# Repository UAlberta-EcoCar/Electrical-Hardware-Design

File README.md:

View this project on [CADLAB.io](https://cadlab.io/project/29517). 

# Electrical-Design-Hardware

**Do not merge branches to main yet, this may be done in the future**

Contains the hardware design for the upcoming prototype vehicle.  Each Branch in this repo has its own board design and schematic files for each car.  Add the entire repo to a filepath ia GitHub Desktop by adding the link into the "Current Repository" panel or with the following via a console:

```
cd Documents\GitHub                                                            #Change your directory where desired
git clone https://github.com/UAlberta-EcoCar/Electrical-Hardware-Design        #Clone the repo
cd Documents\GitHub\Electrical-Hardware-Design                                 #Change your directory into the repo
git branch -r                                                                  #Displays all remote branches, choose the branch you're looking for 
git checkout Relay-Board                                                       #branch that is desired (I used Relay-Board as an example).  
```
After making changes the remote branch can be updated with the following:
```
git add .                                                                      #Adds your modified files to the quene to be committed later
git commit -m "your-commit-message"                                            #Commits the files to a new revision of the branch with a log
git push                                                                       #Pushes the changes to the remote repo

#The following will pull the newest version of the remote repo:
git pull
```

If you want to see your local branches that you pulled or if you want to switch local branches do the following:

```
git branch                                                                     #Shows local branches (add -r for remote branches)
git switch <name-of-branch>                                                    #Switches branch

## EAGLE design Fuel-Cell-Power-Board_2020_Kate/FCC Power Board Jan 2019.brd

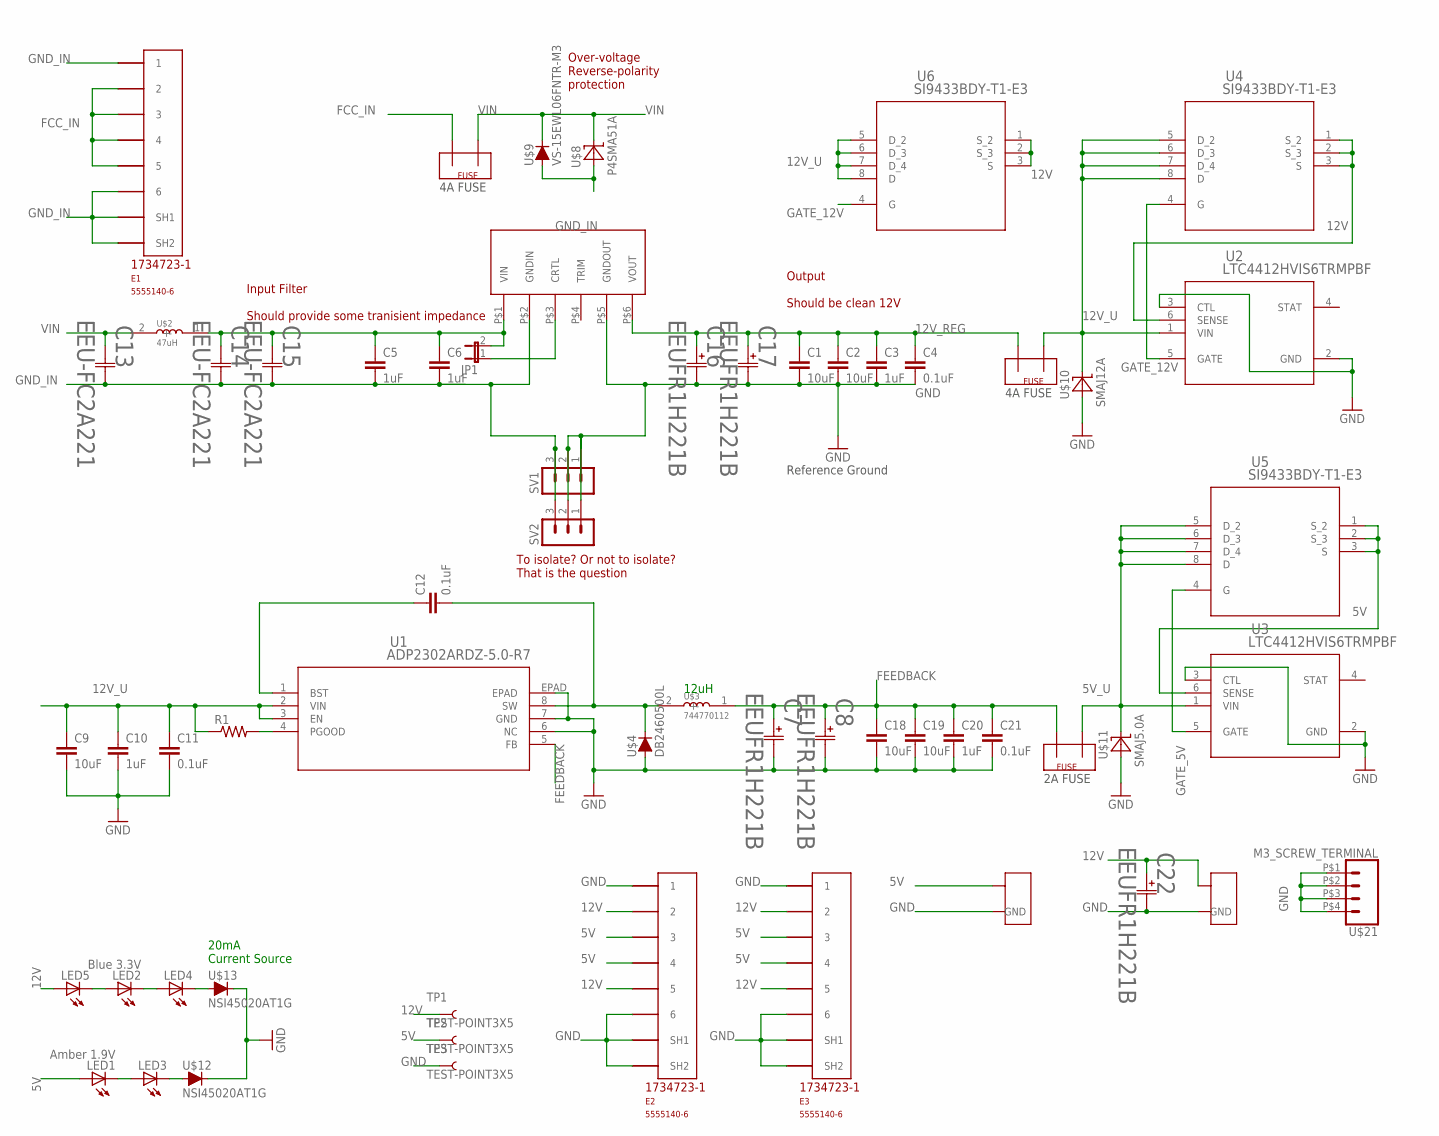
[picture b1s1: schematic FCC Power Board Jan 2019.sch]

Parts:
C1, C2, C9, C18, C19: 10uF; C1210
C3, C10, C20: 1uF; C0805
C4, C11, C12, C21: 0.1uF; C0603
C5, C6: 1uF; C1210
C7, C8, C16, C17, C22: EEUFR1H221B; CAP_PAN_10X16
C13, C14, C15: EEU-FC2A221; CAP_16_X_25
E1, E2, E3: 5555140-6; 1734723-1_RJ11
JP1: JP1E; JP1
LED1: Amber 1.9V; CHIPLED_0805
LED2: Blue 3.3V; CHIPLED_0805
LED3, LED4, LED5: LEDCHIPLED_0805; CHIPLED_0805
R1: R-US_R0603; R0603
SV1, SV2: MA03-1
TP1, TP2, TP3: TEST-POINT3X5; PAD.03X.05
U1: ADP2302ARDZ-5.0-R7; RD_8_1
U2, U3: LTC4412HVIS6TRMPBF; TSOT-23_S6
U4, U5, U6: SI9433BDY-T1-E3; SOIC-N-8_SI
U$1: RPA60-2412SFW_P; RPA60-2412SFW/P
U$2: 47uH; INDUCTOR_SMD_FOOTPRINT
U$3: 744770112; INDUCTOR_SMD_FOOTPRINT
U$4: DB2460500L; SOD123
U$5, U$6, U$7: SHELL2013_FUSEMINI-BLADE; SHELL2013_MINI-BLADE-FUSE
U$8: P4SMA51A; SMA-DO214AC
U$9: VS-15EWL06FNTR-M3; TO252
U$10: SMAJ12A; SMA-DO214AC
U$11: SMAJ5.0A; SMA-DO214AC
U$12, U$13: NSI45020AT1G; SOD123
U$18, U$20: 2X1-CONN; 2X1-MATE-N-LOCK
U$21: M3_SCREW_TERMINAL

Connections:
5V: E2.3, E2.4, E3.3, E3.4, LED1.A, TP2.P$1, U3.6 (SENSE), U5.1 (S_2), U5.2 (S_3), U5.3 (S), U$18.CIRCUIT1
5V_U: U3.1 (VIN), U5.5 (D_2), U5.6 (D_3), U5.7 (D_4), U5.8 (D), U$5.OUT, U$11.K (C)
12V: C22.1 (11), E2.2, E2.5, E3.2, E3.5, LED5.A, TP1.P$1, U2.6 (SENSE), U4.1 (S_2), U4.2 (S_3), U4.3 (S), U6.1 (S_2), U6.2 (S_3), U6.3 (S), U$20.CIRCUIT1
12V_REG: C1.1, C2.1, C3.1, C4.1, C16.1 (11), C17.1 (11), U$1.P$6 (VOUT), U$7.OUT
12V_U: C9.1, C10.1, C11.1, R1.1, U1.2 (VIN), U1.3 (EN), U2.1 (VIN), U4.5 (D_2), U4.6 (D_3), U4.7 (D_4), U4.8 (D), U6.5 (D_2), U6.6 (D_3), U6.7 (D_4), U6.8 (D), U$7.IN, U$10.K (C)
FCC_IN: E1.2, E1.3, E1.4, E1.5, U$6.OUT
FEEDBACK: C7.1 (11), C8.1 (11), C18.1, C19.1, C20.1, C21.1, U1.5 (FB), U$3.1 (+), U$5.IN
GATE_5V: U3.5 (GATE), U5.4 (G)
GATE_12V: U2.5 (GATE), U4.4 (G), U6.4 (G)
GND: C1.2, C2.2, C3.2, C4.2, C7.2 (22), C8.2 (22), C9.2, C10.2, C11.2, C16.2 (22), C17.2 (22), C18.2, C19.2, C20.2, C21.2, C22.2 (22), E2.1, E2.6, E2.SH1, E2.SH2, E3.1, E3.6, E3.SH1, E3.SH2, SV1.1, SV1.2, SV2.1, SV2.2, TP3.P$1, U1.6 (NC), U1.7 (GND), U1.EPAD, U2.2 (GND), U2.3 (CTL), U3.2 (GND), U3.3 (CTL), U$1.P$5 (GNDOUT), U$4.A, U$10.A, U$11.A, U$12.C, U$13.C, U$18.GND, U$20.GND, U$21.P$1 (1), U$21.P$2 (2), U$21.P$3 (3), U$21.P$4 (4)
GND_IN: C5.2, C6.2, C13.2 (22), C14.2 (22), C15.2 (22), E1.1, E1.6, E1.SH1, E1.SH2, SV1.3, SV2.3, U$1.P$2 (GNDIN), U$8.A, U$9.1 (A), U$9.2 (A)
unnamed: JP1.1, U$1.P$3 (CRTL)
unnamed: C12.1, U1.1 (BST)
unnamed: C12.2, U1.8 (SW), U$3.2 (-), U$4.C
unnamed: R1.2, U1.4 (PGOOD)
unnamed: LED1.C, LED3.A
unnamed: LED3.C, U$12.A
unnamed: LED4.C, U$13.A
unnamed: LED2.C, LED4.A
unnamed: LED2.A, LED5.C
unnamed: C5.1, C6.1, C14.1 (11), C15.1 (11), JP1.2, U$1.P$1 (VIN), U$2.1 (+)
VIN: C13.1 (11), U$2.2 (-), U$6.IN, U$8.K (C), U$9.3 (C)

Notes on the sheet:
Input Filter Should provide some tranisient impedance
Output Should be clean 12V
To isolate? Or not to isolate? That is the question
4A FUSE
Reference Ground
Over-voltage Reverse-polarity protection
12uH
2A FUSE
20mA Current Source

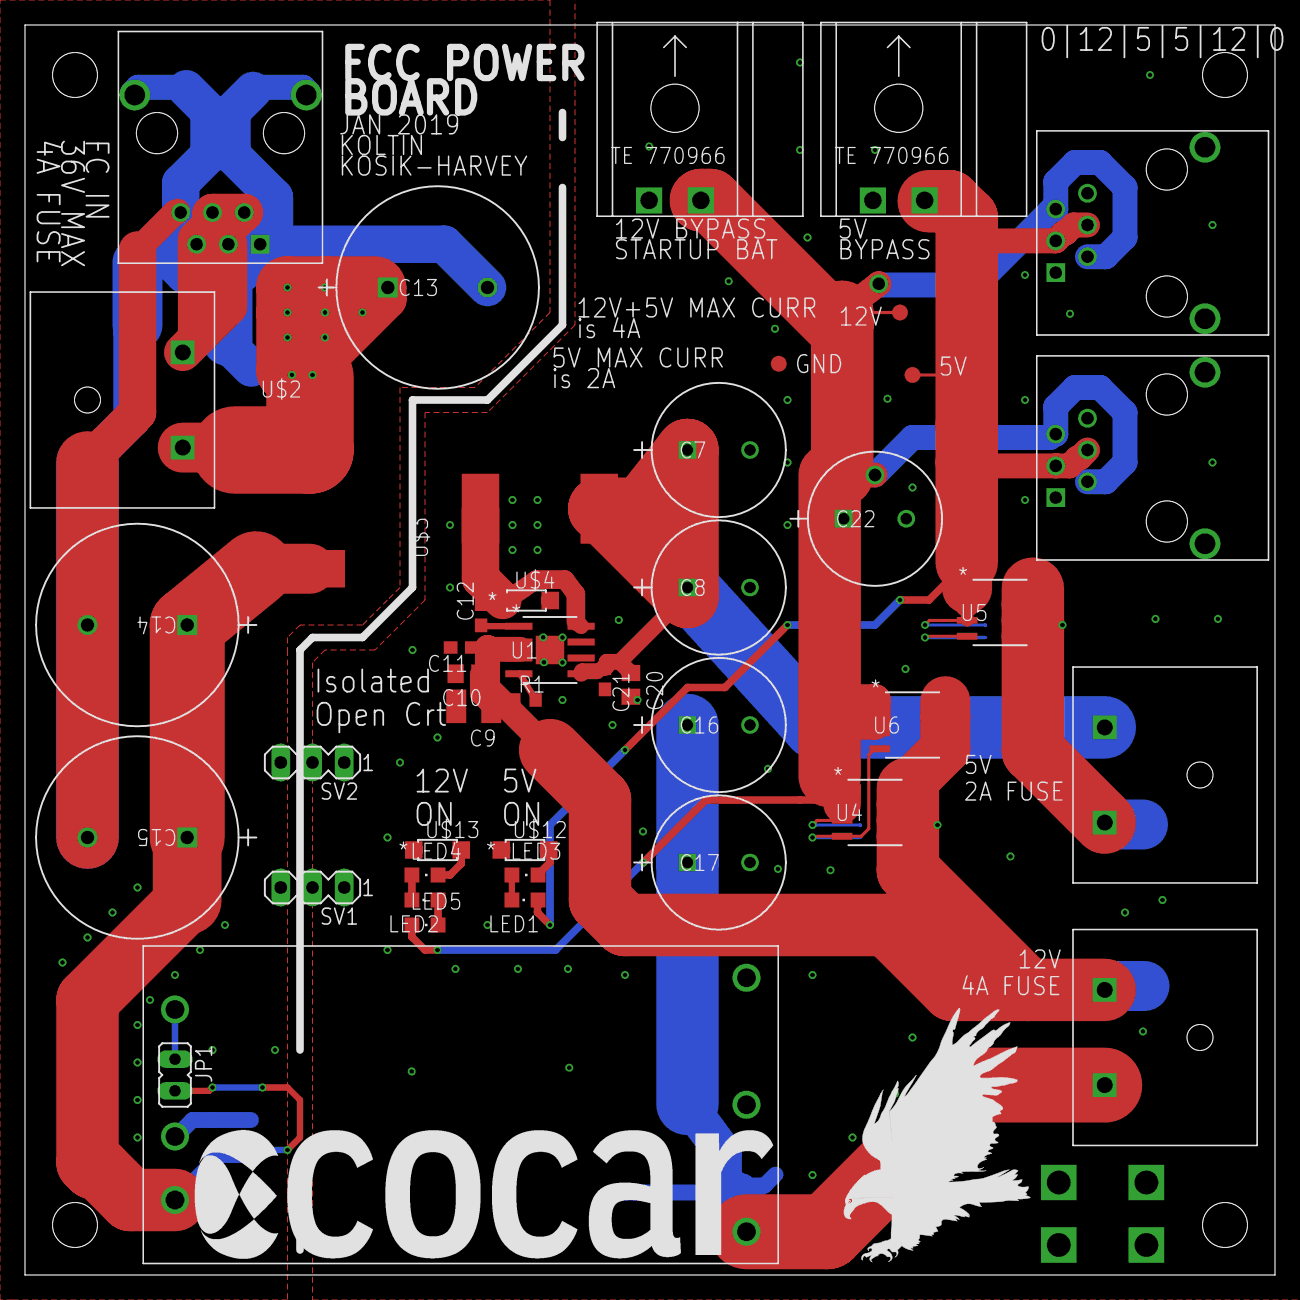
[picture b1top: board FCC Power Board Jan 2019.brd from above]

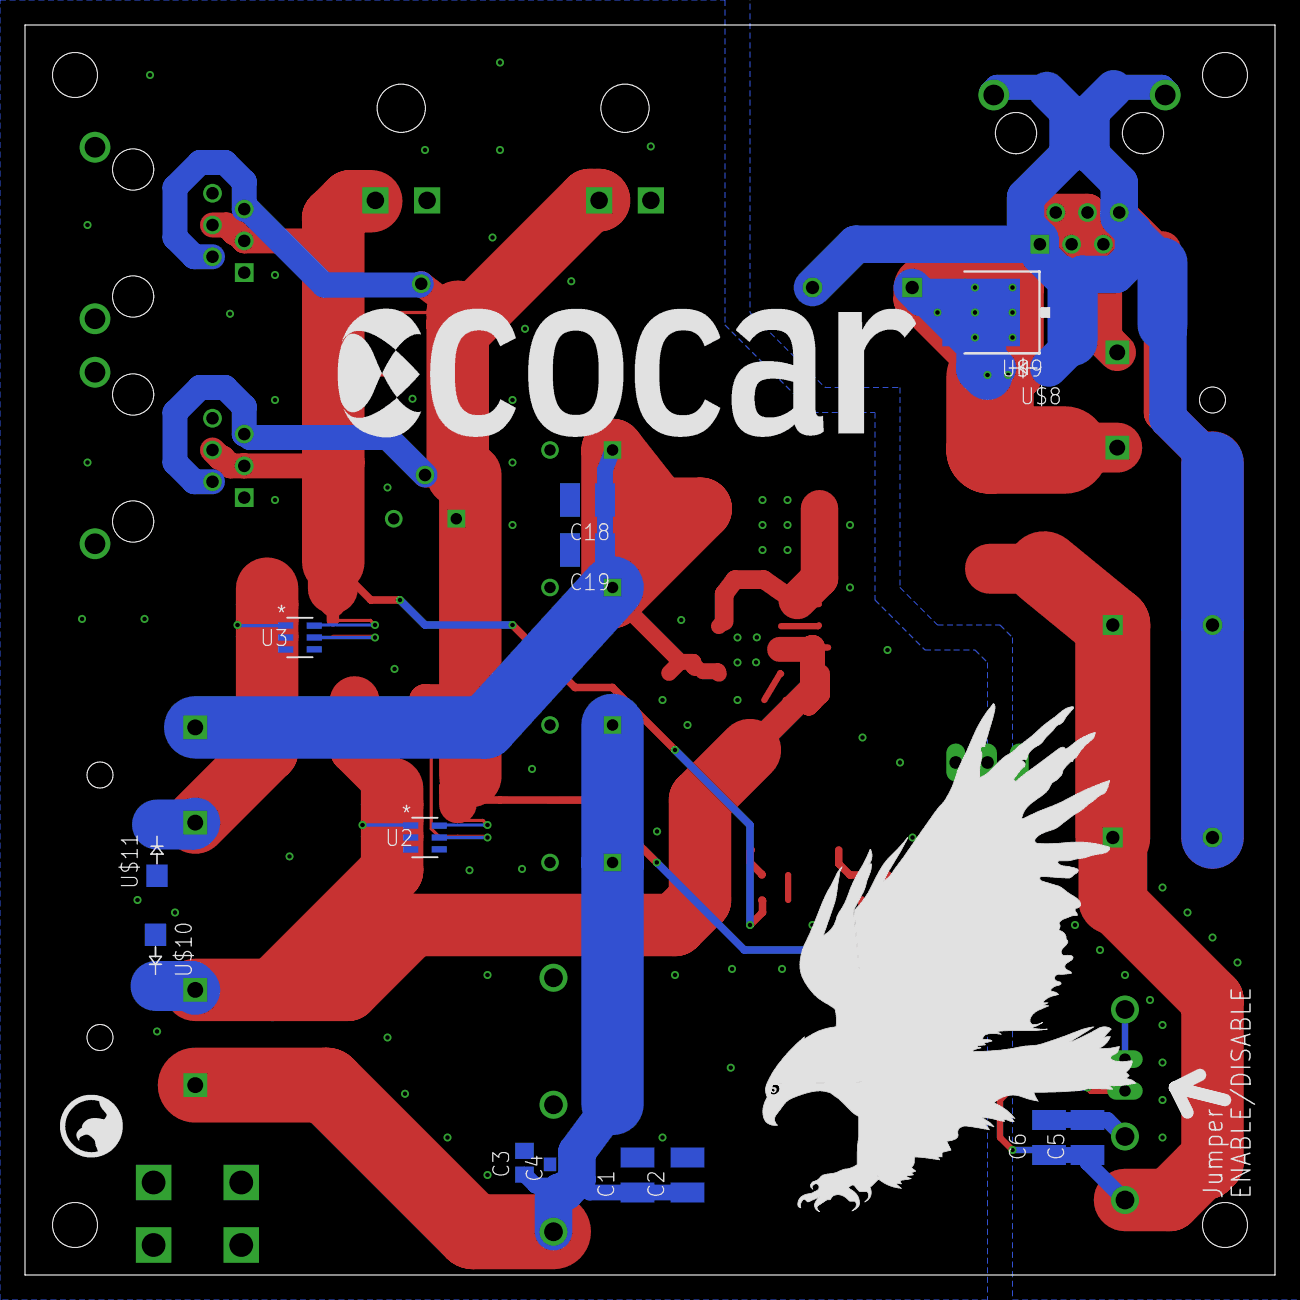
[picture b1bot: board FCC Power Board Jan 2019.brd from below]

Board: 2 copper layers, 100.0 x 100.0 mm, 64 parts (17 on the bottom side), 22 nets.

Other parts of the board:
U$14, U$15: ECOCAR_LOGO_2018
U$16: CS-2016-LOGO-5MM
U$17: EAGLE-PLC-30MM
U$19: EAGLE-PLC-15MM

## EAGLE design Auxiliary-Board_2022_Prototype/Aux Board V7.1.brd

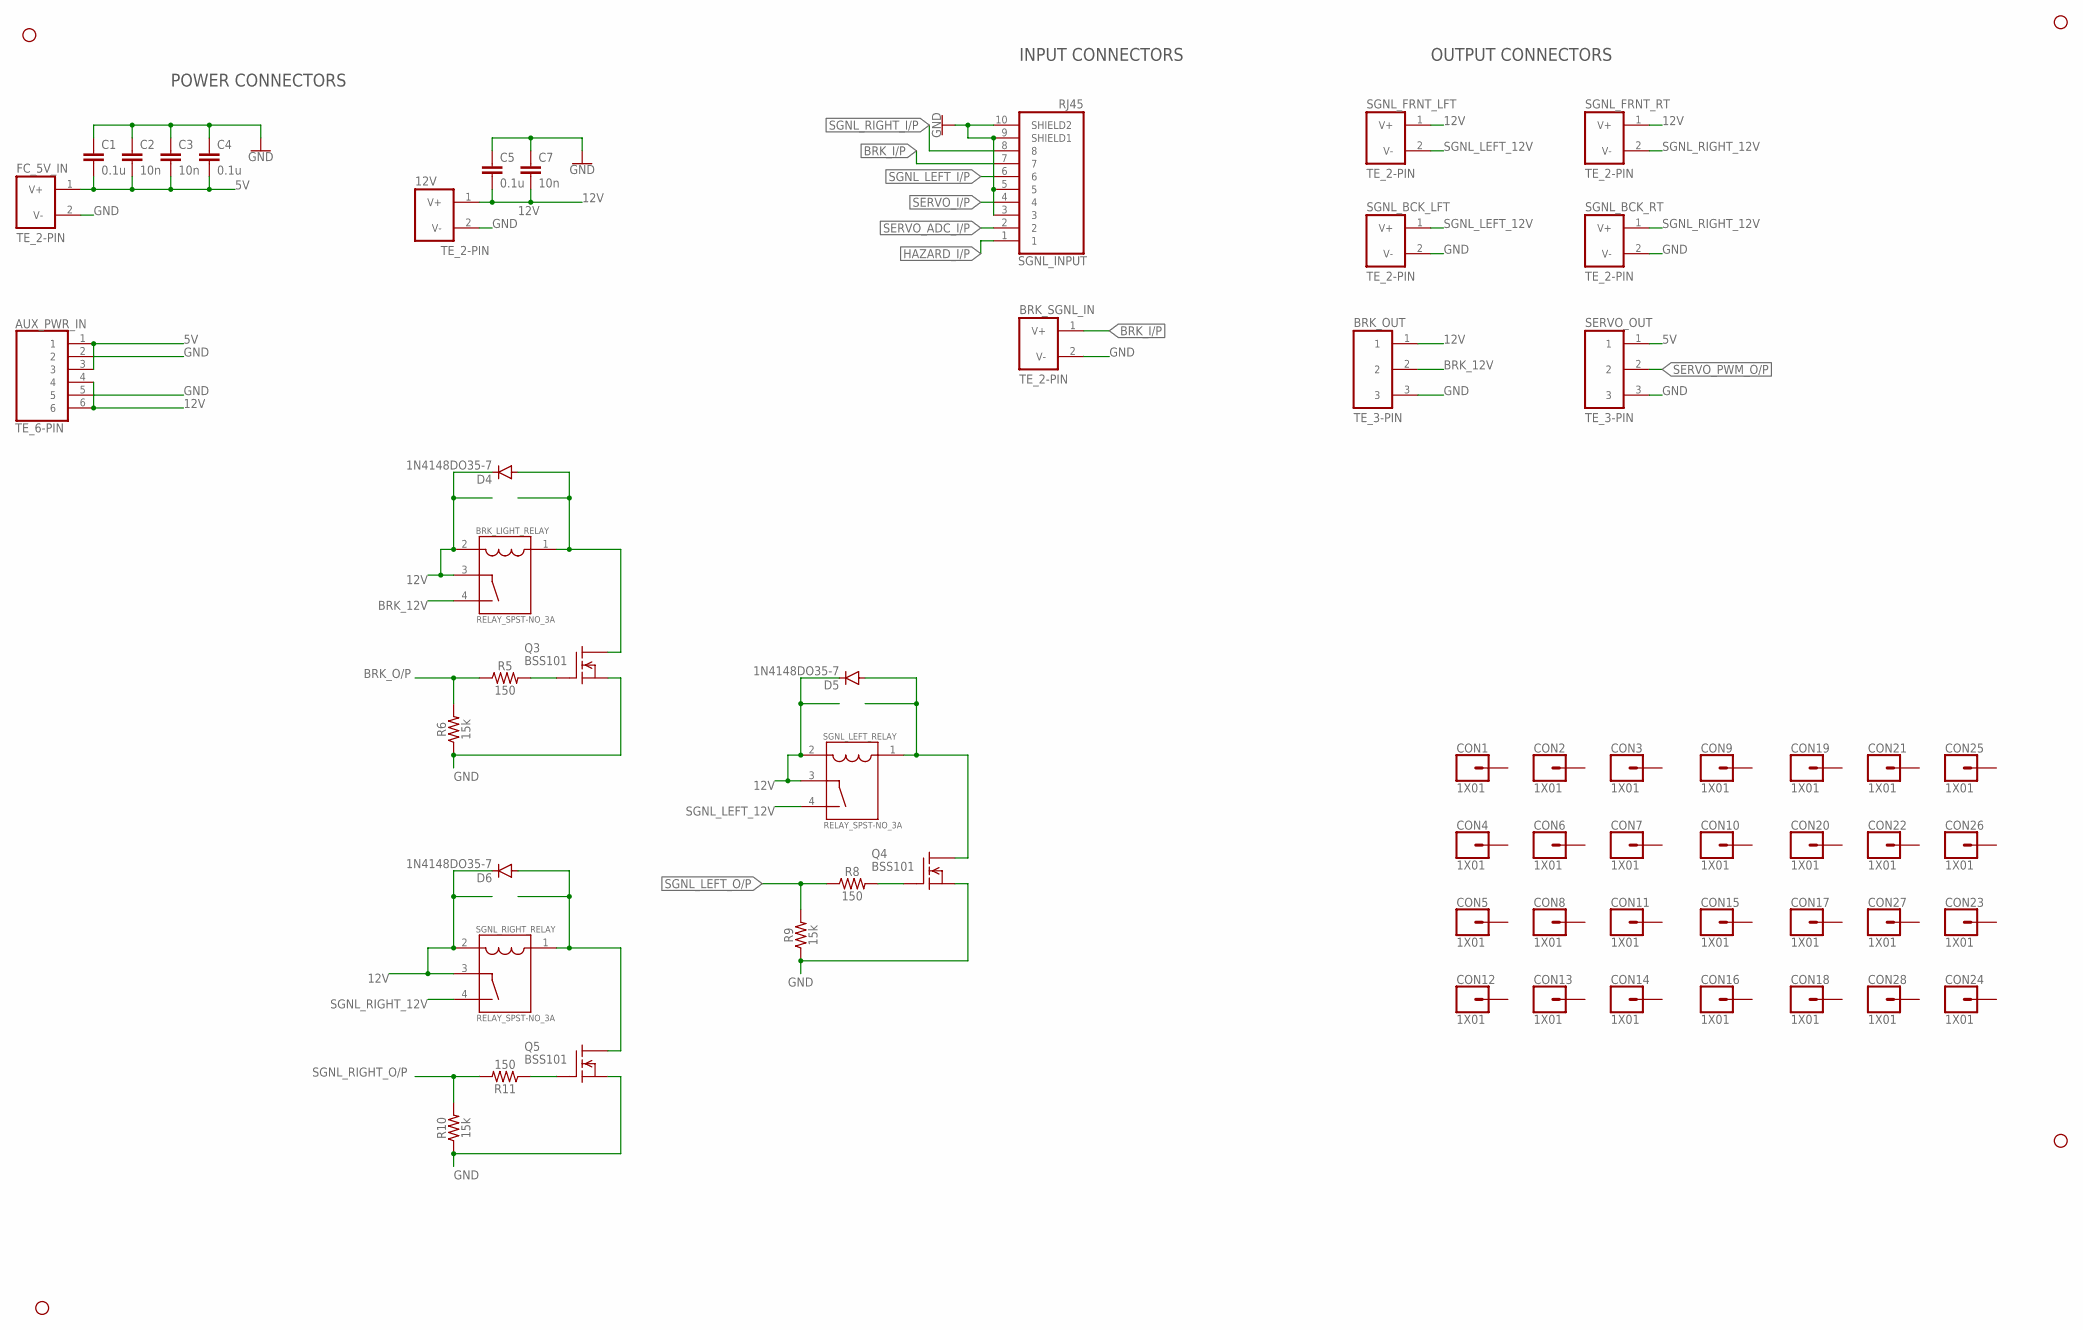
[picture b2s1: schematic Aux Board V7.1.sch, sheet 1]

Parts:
12V: TE_2-PIN
AUX_PWR_IN: TE_6-PIN
BRK_LIGHT_RELAY: RELAY_SPST-NO_3A; TE_1-1721081-2
BRK_OUT: TE_3-PIN
BRK_SGNL_IN: TE_2-PIN
C1, C4, C5: 0.1u; 0805
C2, C3, C7: 10n; 0805
CON1, CON2, CON3, CON4, CON5, CON6, CON7, CON8, CON9, CON10, CON11, CON12, CON13, CON14, CON15, CON16, CON17, CON18, CON19, CON20, CON21, CON22, CON23, CON24, CON25, CON26, CON27, CON28: 1X01
D4, D5, D6: 1N4148DO35-7; DO35-7
FC_5V_IN: TE_2-PIN
H1, H2, H3, H4: STAND-OFF
Q3, Q4, Q5: BSS101; TO92
R5, R8, R11: 150; 0805
R6, R9, R10: 15k; 0805
SERVO_OUT: TE_3-PIN
SGNL_BCK_LFT: TE_2-PIN
SGNL_BCK_RT: TE_2-PIN
SGNL_FRNT_LFT: TE_2-PIN
SGNL_FRNT_RT: TE_2-PIN
SGNL_INPUT: RJ45
SGNL_LEFT_RELAY: RELAY_SPST-NO_3A; TE_1-1721081-2
SGNL_RIGHT_RELAY: RELAY_SPST-NO_3A; TE_1-1721081-2

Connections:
5V: AUX_PWR_IN.1, AUX_PWR_IN.3, C1.2, C2.2, C3.2, C4.2, FC_5V_IN.1 (V+), SERVO_OUT.1; also elsewhere on the board
12V: 12V.1 (V+), AUX_PWR_IN.4, AUX_PWR_IN.6, BRK_LIGHT_RELAY.2, BRK_LIGHT_RELAY.3, BRK_OUT.1, C5.2, C7.2, D4.C, D5.C, D6.C, SGNL_FRNT_LFT.1 (V+), SGNL_FRNT_RT.1 (V+), SGNL_LEFT_RELAY.2, SGNL_LEFT_RELAY.3, SGNL_RIGHT_RELAY.2, SGNL_RIGHT_RELAY.3
BRK_12V: BRK_LIGHT_RELAY.4, BRK_OUT.2
BRK_I/P: BRK_SGNL_IN.1 (V+), SGNL_INPUT.7; also elsewhere on the board
BRK_O/P: R5.1, R6.2; also elsewhere on the board
GND: 12V.2 (V-), AUX_PWR_IN.2, AUX_PWR_IN.5, BRK_OUT.3, BRK_SGNL_IN.2 (V-), C1.1, C2.1, C3.1, C4.1, C5.1, C7.1, FC_5V_IN.2 (V-), Q3.1 (S), Q4.1 (S), Q5.1 (S), R6.1, R9.1, R10.1, SERVO_OUT.3, SGNL_BCK_LFT.2 (V-), SGNL_BCK_RT.2 (V-), SGNL_INPUT.3, SGNL_INPUT.5, SGNL_INPUT.9 (SHIELD1), SGNL_INPUT.10 (SHIELD2); also elsewhere on the board
HAZARD_I/P: SGNL_INPUT.1; also elsewhere on the board
unnamed: BRK_LIGHT_RELAY.1, D4.A, Q3.3 (D)
unnamed: Q3.2 (G), R5.2
unnamed: D5.A, Q4.3 (D), SGNL_LEFT_RELAY.1
unnamed: Q4.2 (G), R8.2
unnamed: D6.A, Q5.3 (D), SGNL_RIGHT_RELAY.1
unnamed: Q5.2 (G), R11.1
SERVO_ADC_I/P: SGNL_INPUT.2; also elsewhere on the board
SERVO_I/P: SGNL_INPUT.4; also elsewhere on the board
SERVO_PWM_O/P: SERVO_OUT.2; also elsewhere on the board
SGNL_LEFT_12V: SGNL_BCK_LFT.1 (V+), SGNL_FRNT_LFT.2 (V-), SGNL_LEFT_RELAY.4
SGNL_LEFT_I/P: SGNL_INPUT.6; also elsewhere on the board
SGNL_LEFT_O/P: R8.1, R9.2; also elsewhere on the board
SGNL_RIGHT_12V: SGNL_BCK_RT.1 (V+), SGNL_FRNT_RT.2 (V-), SGNL_RIGHT_RELAY.4
SGNL_RIGHT_I/P: SGNL_INPUT.8; also elsewhere on the board
SGNL_RIGHT_O/P: R10.2, R11.2; also elsewhere on the board

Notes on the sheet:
OUTPUT CONNECTORS
POWER CONNECTORS
INPUT CONNECTORS

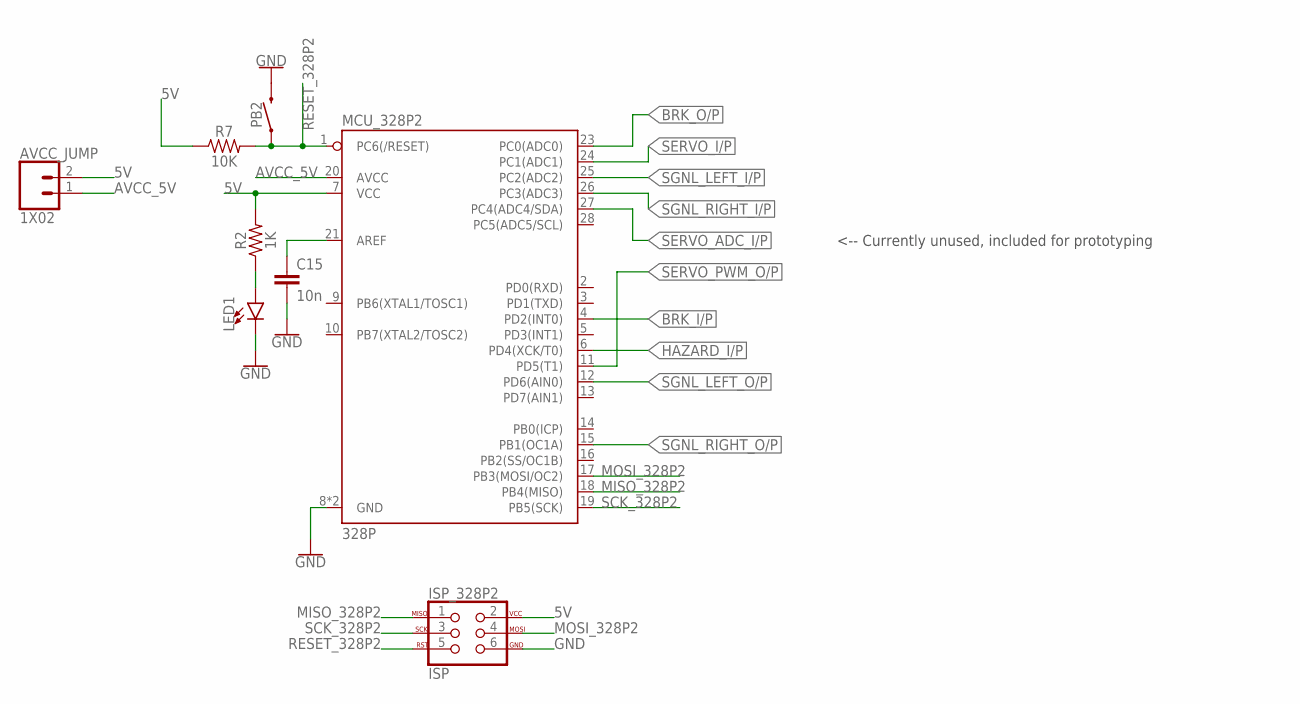
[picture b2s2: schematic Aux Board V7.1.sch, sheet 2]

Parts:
AVCC_JUMP: 1X02
C15: 10n; 0805
ISP_328P2: ISP; ISP_CONNECTOR
LED1: LED_0805; 0805_LED
MCU_328P2: 328P; DIP28
PB2: PUSHBUTTON
R2: 1K; 0805
R7: 10K; 0805

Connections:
5V: AVCC_JUMP.2, ISP_328P2.2, MCU_328P2.7 (VCC), R2.2, R7.1; also elsewhere on the board
AREF: C15.1, MCU_328P2.21 (AREF)
AVCC_5V: AVCC_JUMP.1, MCU_328P2.20 (AVCC)
BRK_I/P: MCU_328P2.4 (PD2(INT0)); also elsewhere on the board
BRK_O/P: MCU_328P2.23 (PC0(ADC0)); also elsewhere on the board
GND: C15.2, ISP_328P2.6, LED1.2 (C), MCU_328P2.8 (GND), MCU_328P2.22 (GND), PB2.3 (2), PB2.4 (2); also elsewhere on the board
HAZARD_I/P: MCU_328P2.6 (PD4(XCK/T0)); also elsewhere on the board
MISO_328P2: ISP_328P2.1, MCU_328P2.18 (PB4(MISO))
MOSI_328P2: ISP_328P2.4, MCU_328P2.17 (PB3(MOSI/OC2))
unnamed: LED1.1 (A), R2.1
RESET_328P2: ISP_328P2.5, MCU_328P2.1 (PC6(/RESET)), PB2.1, PB2.2 (1), R7.2
SCK_328P2: ISP_328P2.3, MCU_328P2.19 (PB5(SCK))
SERVO_ADC_I/P: MCU_328P2.27 (PC4(ADC4/SDA)); also elsewhere on the board
SERVO_I/P: MCU_328P2.24 (PC1(ADC1)); also elsewhere on the board
SERVO_PWM_O/P: MCU_328P2.11 (PD5(T1)); also elsewhere on the board
SGNL_LEFT_I/P: MCU_328P2.25 (PC2(ADC2)); also elsewhere on the board
SGNL_LEFT_O/P: MCU_328P2.12 (PD6(AIN0)); also elsewhere on the board
SGNL_RIGHT_I/P: MCU_328P2.26 (PC3(ADC3)); also elsewhere on the board
SGNL_RIGHT_O/P: MCU_328P2.15 (PB1(OC1A)); also elsewhere on the board

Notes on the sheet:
<-- Currently unused, included for prototyping

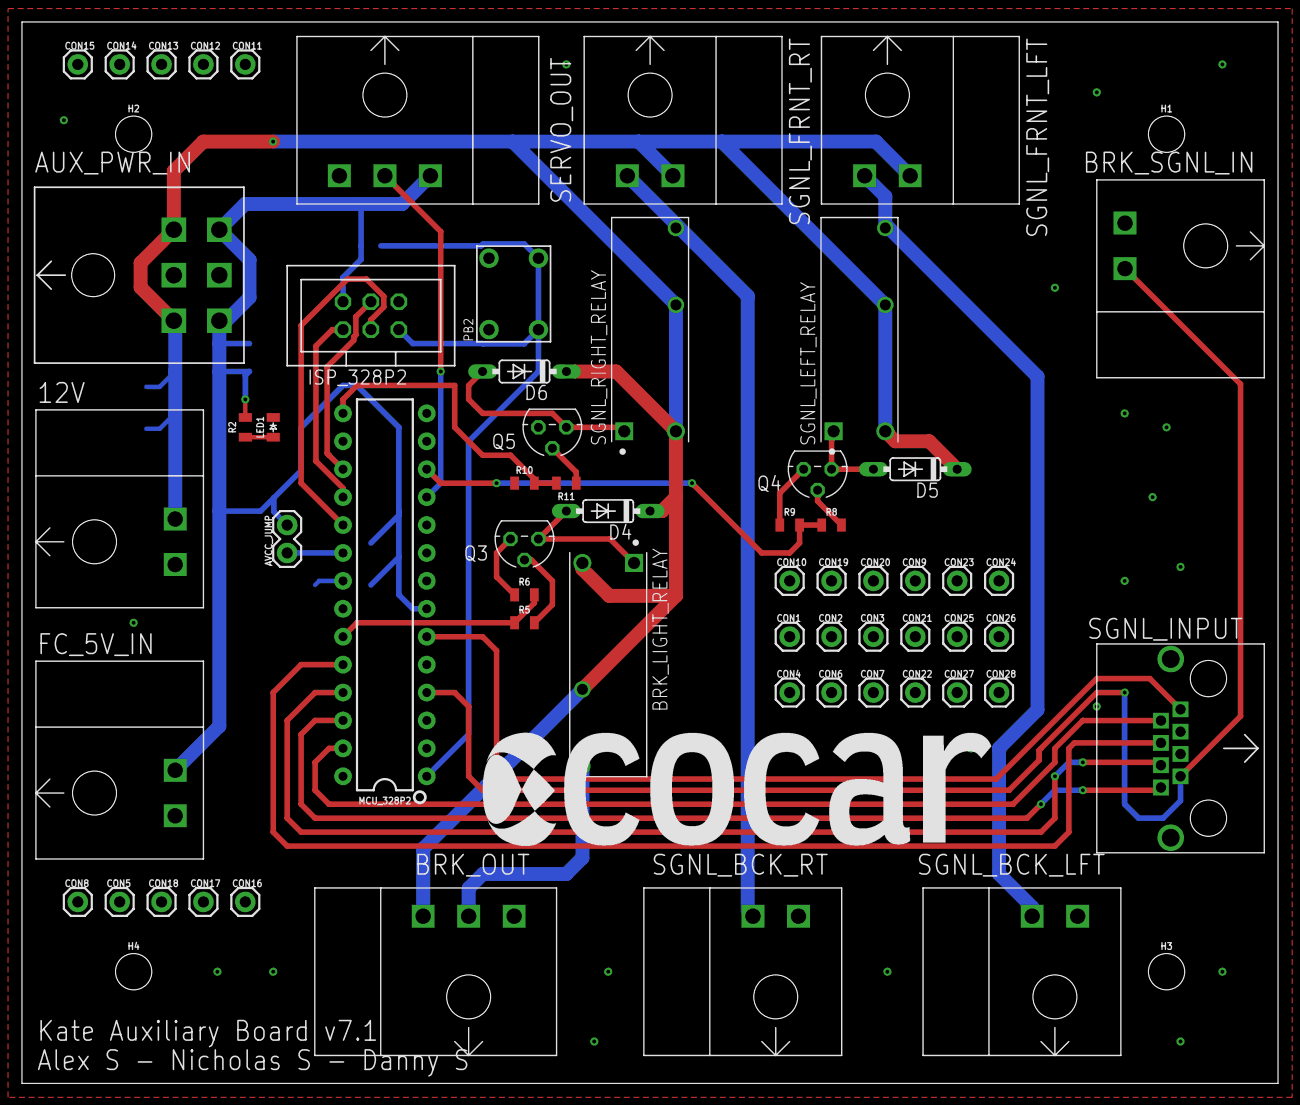
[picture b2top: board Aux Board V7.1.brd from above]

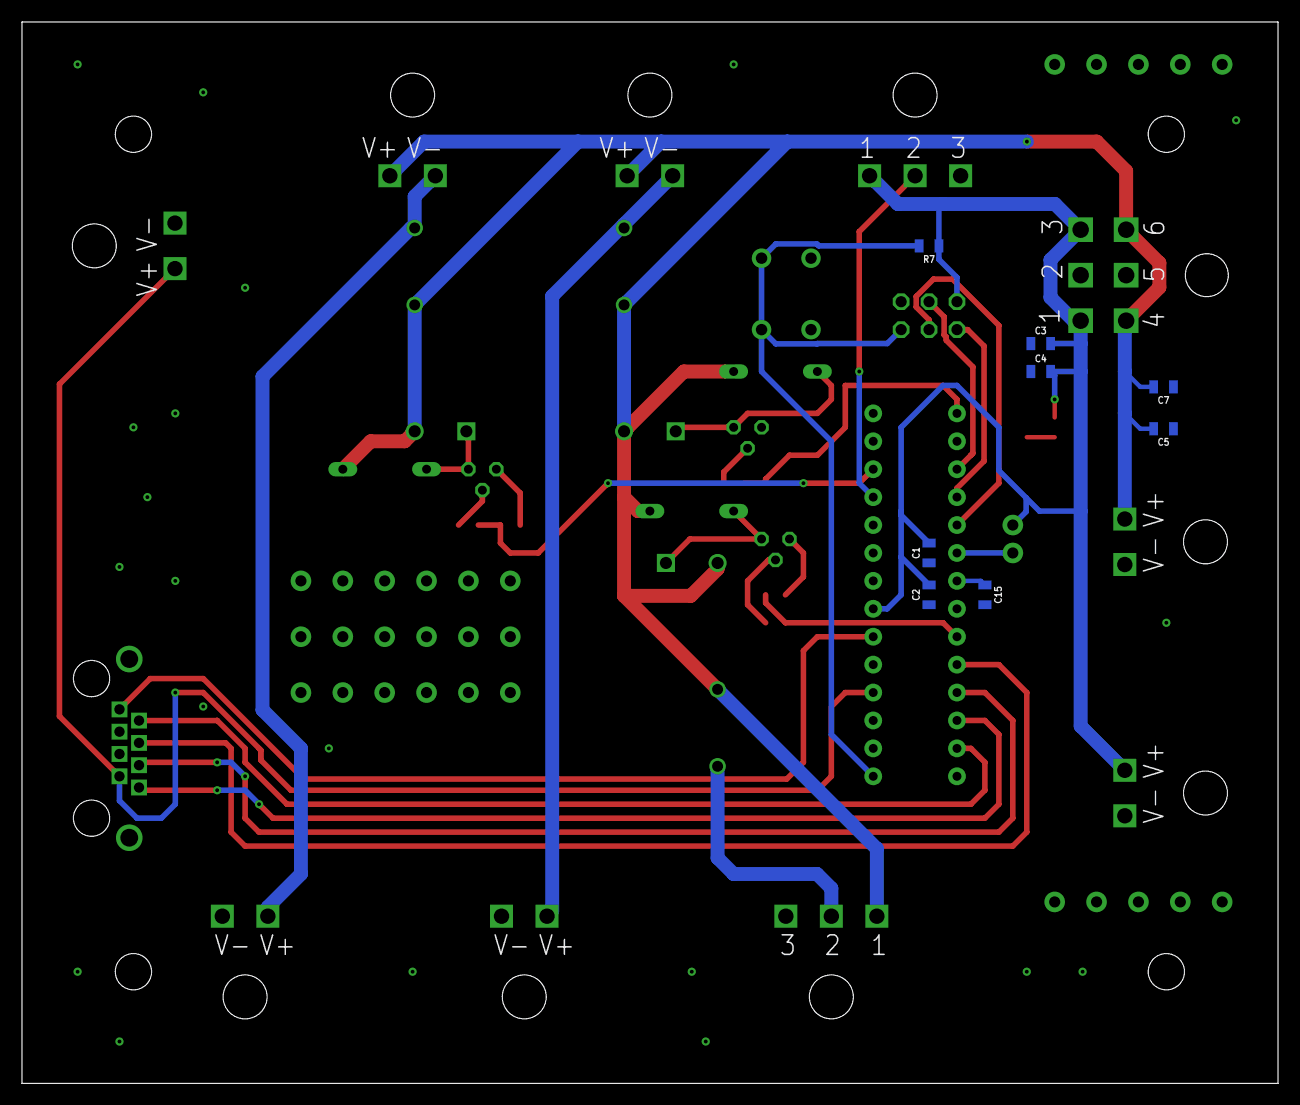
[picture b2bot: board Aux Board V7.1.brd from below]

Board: 2 copper layers, 114.3 x 96.6 mm, 73 parts (8 on the bottom side), 29 nets.

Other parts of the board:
U$1: ECOCAR_LOGO_2018

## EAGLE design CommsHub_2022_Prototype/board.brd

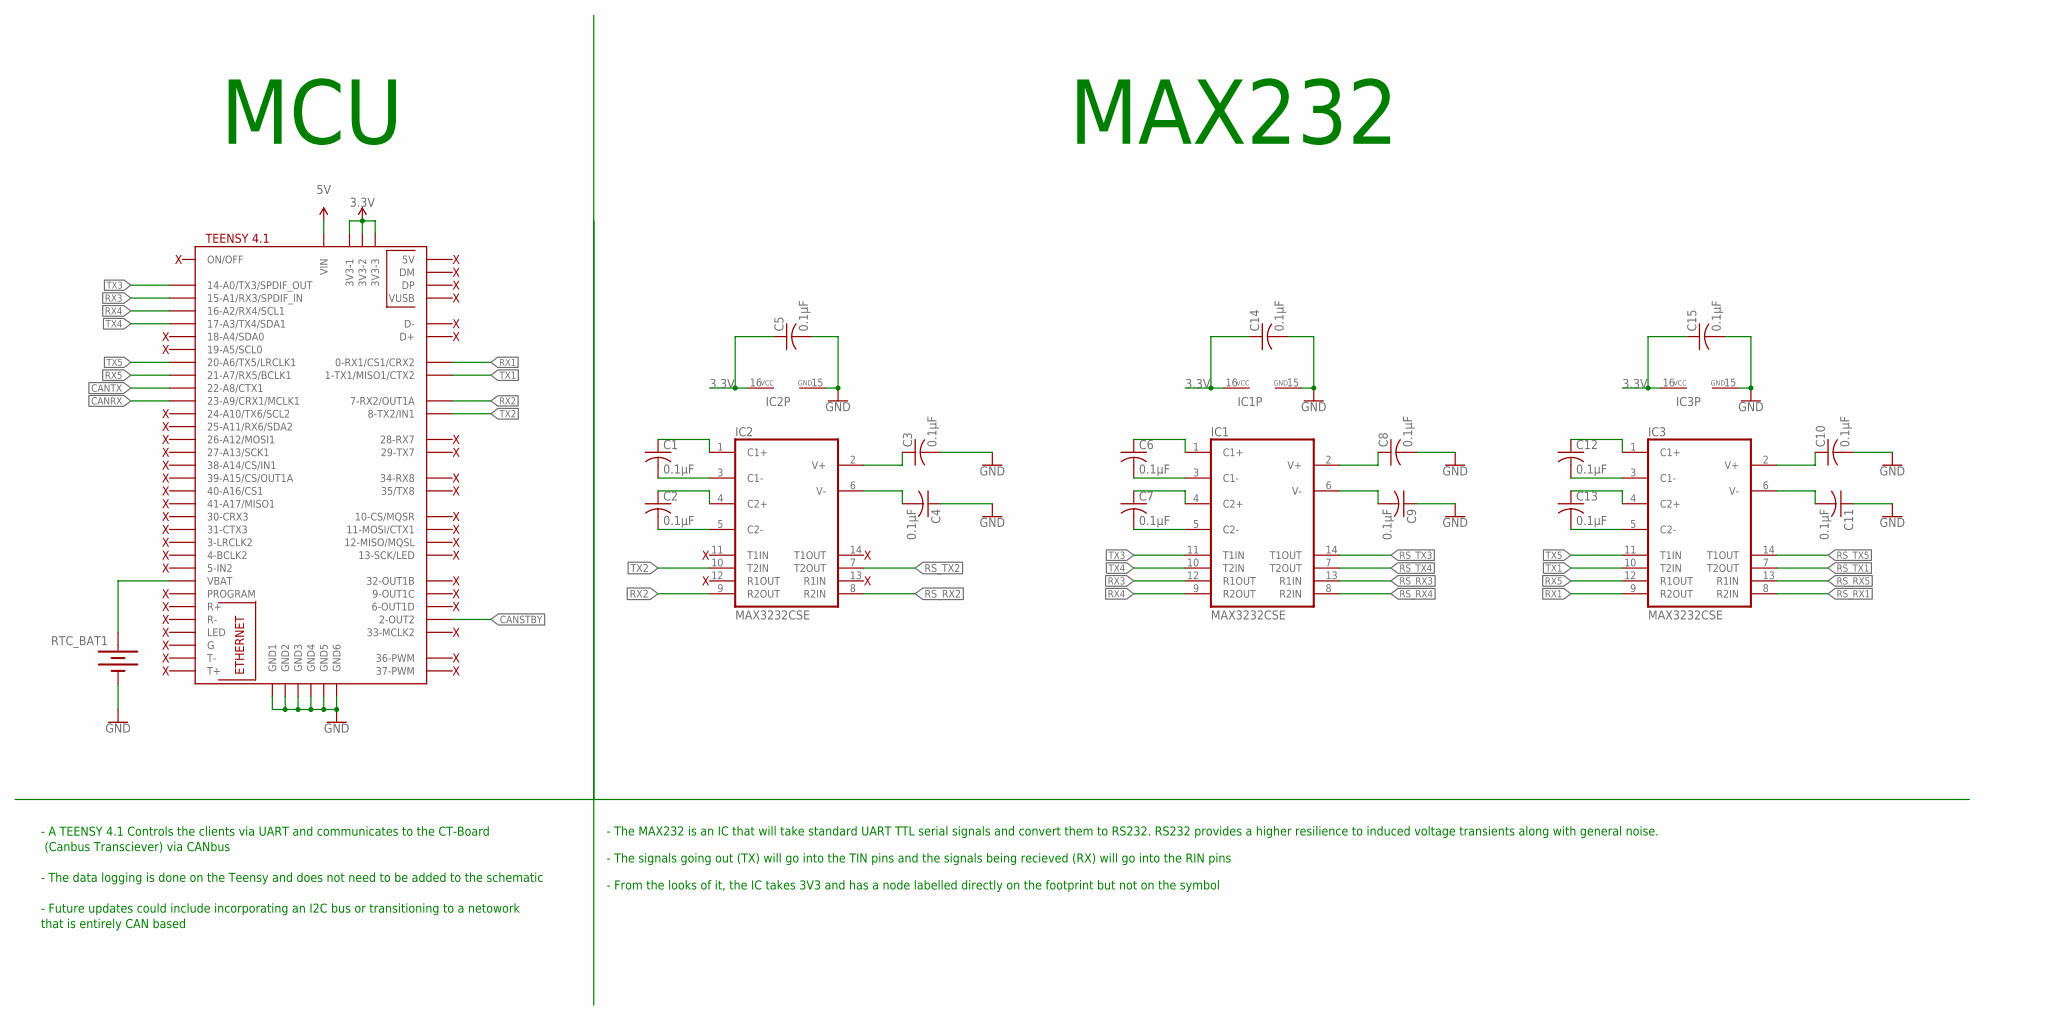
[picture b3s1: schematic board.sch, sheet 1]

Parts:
C1, C2, C3, C4, C5, C6, C7, C8, C9, C10, C11, C12, C13, C14, C15: 0.1µF; C0805
IC1, IC2, IC3: MAX3232CSE; SO16
RTC_BAT1: BATTERY-20MM_PTH; BATTCOM_20MM_PTH
U$1: TEENSY41

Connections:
3.3V: C5.1, C14.1, C15.1, IC1.16 (VCC), IC2.16 (VCC), IC3.16 (VCC), U$1.3V3-1, U$1.3V3-2, U$1.3V3-3; also elsewhere on the board
CANRX: U$1.23-A9/CRX1/MCLK1; also elsewhere on the board
CANSTBY: U$1.2-OUT2; also elsewhere on the board
CANTX: U$1.22-A8/CTX1; also elsewhere on the board
GND: C3.2, C4.1, C5.2, C8.2, C9.1, C10.2, C11.1, C14.2, C15.2, IC1.15 (GND), IC2.15 (GND), IC3.15 (GND), RTC_BAT1.2 (-), U$1.GND1, U$1.GND2, U$1.GND3, U$1.GND4, U$1.GND5, U$1.GND6; also elsewhere on the board
unnamed: C1.1, IC2.1 (C1+)
unnamed: C1.2, IC2.3 (C1-)
unnamed: C2.1, IC2.4 (C2+)
unnamed: C2.2, IC2.5 (C2-)
unnamed: C3.1, IC2.2 (V+)
unnamed: C4.2, IC2.6 (V-)
unnamed: C6.2, IC1.3 (C1-)
unnamed: C7.2, IC1.5 (C2-)
unnamed: C6.1, IC1.1 (C1+)
unnamed: C7.1, IC1.4 (C2+)
unnamed: C8.1, IC1.2 (V+)
unnamed: C9.2, IC1.6 (V-)
unnamed: C10.1, IC3.2 (V+)
unnamed: C11.2, IC3.6 (V-)
unnamed: C12.2, IC3.3 (C1-)
unnamed: C13.2, IC3.5 (C2-)
unnamed: C12.1, IC3.1 (C1+)
unnamed: C13.1, IC3.4 (C2+)
unnamed: RTC_BAT1.1 (+), U$1.VBAT
RS_RX1: IC3.8 (R2IN); also elsewhere on the board
RS_RX2: IC2.8 (R2IN); also elsewhere on the board
RS_RX3: IC1.13 (R1IN); also elsewhere on the board
RS_RX4: IC1.8 (R2IN); also elsewhere on the board
RS_RX5: IC3.13 (R1IN); also elsewhere on the board
RS_TX1: IC3.7 (T2OUT); also elsewhere on the board
RS_TX2: IC2.7 (T2OUT); also elsewhere on the board
RS_TX3: IC1.14 (T1OUT); also elsewhere on the board
RS_TX4: IC1.7 (T2OUT); also elsewhere on the board
RS_TX5: IC3.14 (T1OUT); also elsewhere on the board
RX1: IC3.9 (R2OUT), U$1.0-RX1/CS1/CRX2; also elsewhere on the board
RX2: IC2.9 (R2OUT), U$1.7-RX2/OUT1A; also elsewhere on the board
RX3: IC1.12 (R1OUT), U$1.15-A1/RX3/SPDIF_IN; also elsewhere on the board
RX4: IC1.9 (R2OUT), U$1.16-A2/RX4/SCL1; also elsewhere on the board
RX5: IC3.12 (R1OUT), U$1.21-A7/RX5/BCLK1; also elsewhere on the board
TX1: IC3.10 (T2IN), U$1.1-TX1/MISO1/CTX2; also elsewhere on the board
TX2: IC2.10 (T2IN), U$1.8-TX2/IN1; also elsewhere on the board
TX3: IC1.11 (T1IN), U$1.14-A0/TX3/SPDIF_OUT; also elsewhere on the board
TX4: IC1.10 (T2IN), U$1.17-A3/TX4/SDA1; also elsewhere on the board
TX5: IC3.11 (T1IN), U$1.20-A6/TX5/LRCLK1; also elsewhere on the board

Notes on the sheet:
MCU
MAX232
- A TEENSY 4.1 Controls the clients via UART and communicates to the CT-Board (Canbus Transciever) via CANbus - The data logging is done on the Teensy and does not need to be added to the schematic - Future updates could include incorporating an I2C bus or transitioning to a netowork that is entire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
- The MAX232 is an IC that will take standard UART TTL serial signals and convert them to RS232. RS232 provides a higher resilience to induced voltage transients along with general noise. - The signals going out (TX) will go into the TIN pins and the signals being recieved (RX) will go into the RIN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

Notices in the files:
parts and their libraries:
SparkFun-PowerSymbols: Licensing: Creative Commons ShareAlike 4.0 International - https://creativecommons.org/licenses/by-sa/4.0
SparkFun-Aesthetics: Released under the Creative Commons Attribution Share-Alike 4.0 License
SparkFun-Aesthetics: https://creativecommons.org/licenses/by-sa/4.0
